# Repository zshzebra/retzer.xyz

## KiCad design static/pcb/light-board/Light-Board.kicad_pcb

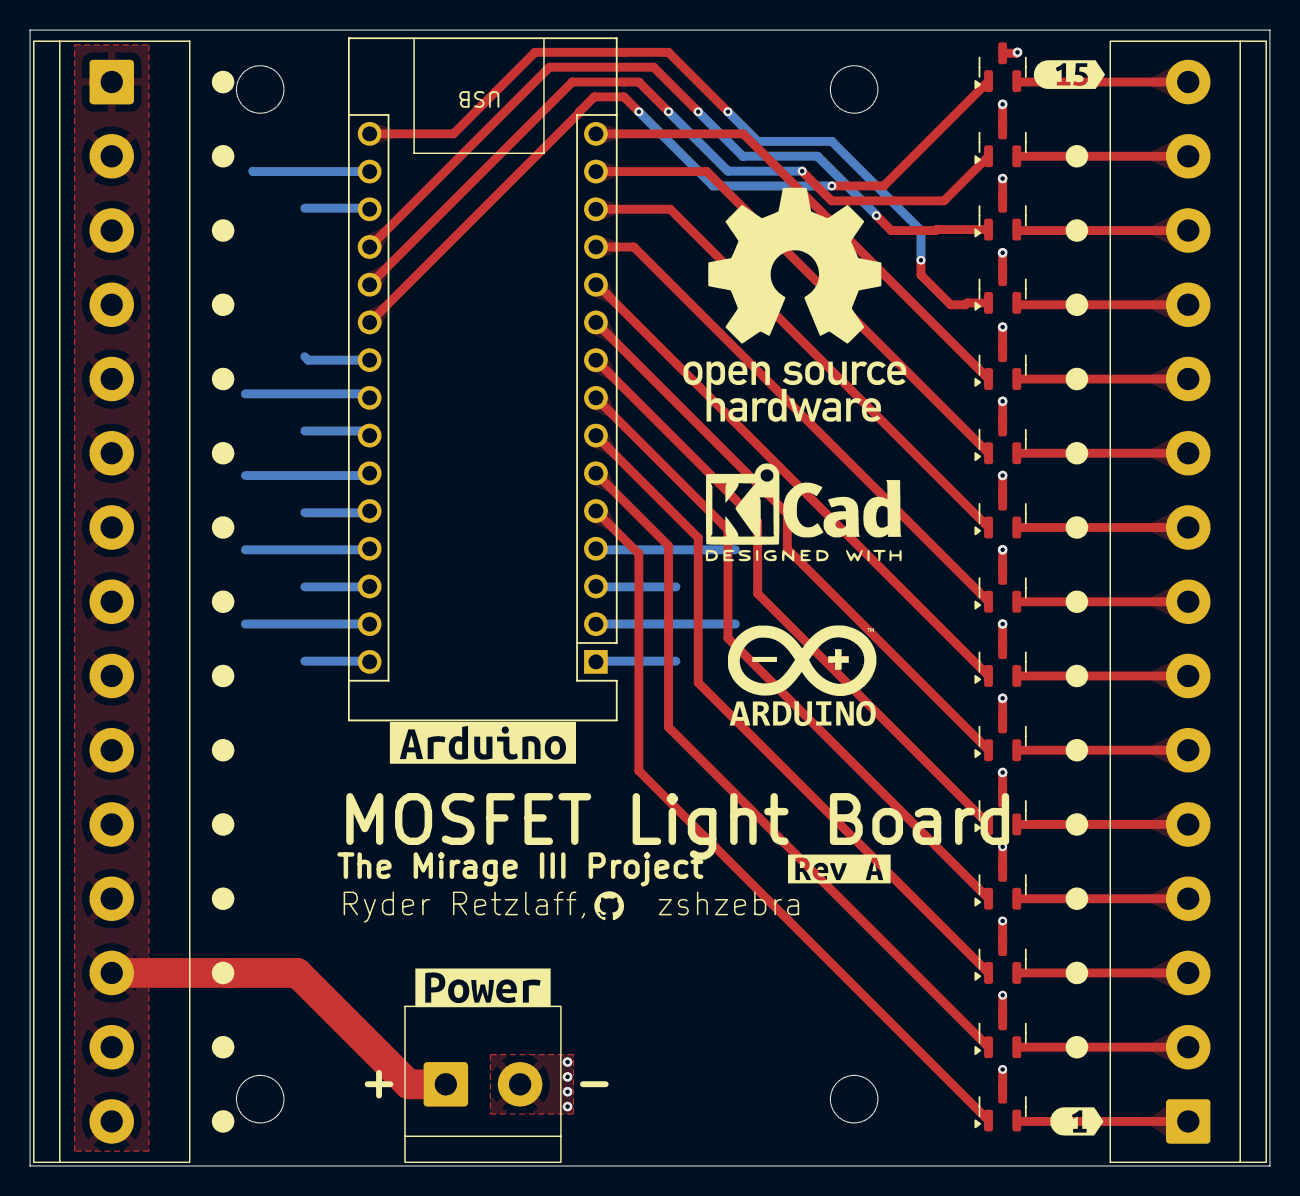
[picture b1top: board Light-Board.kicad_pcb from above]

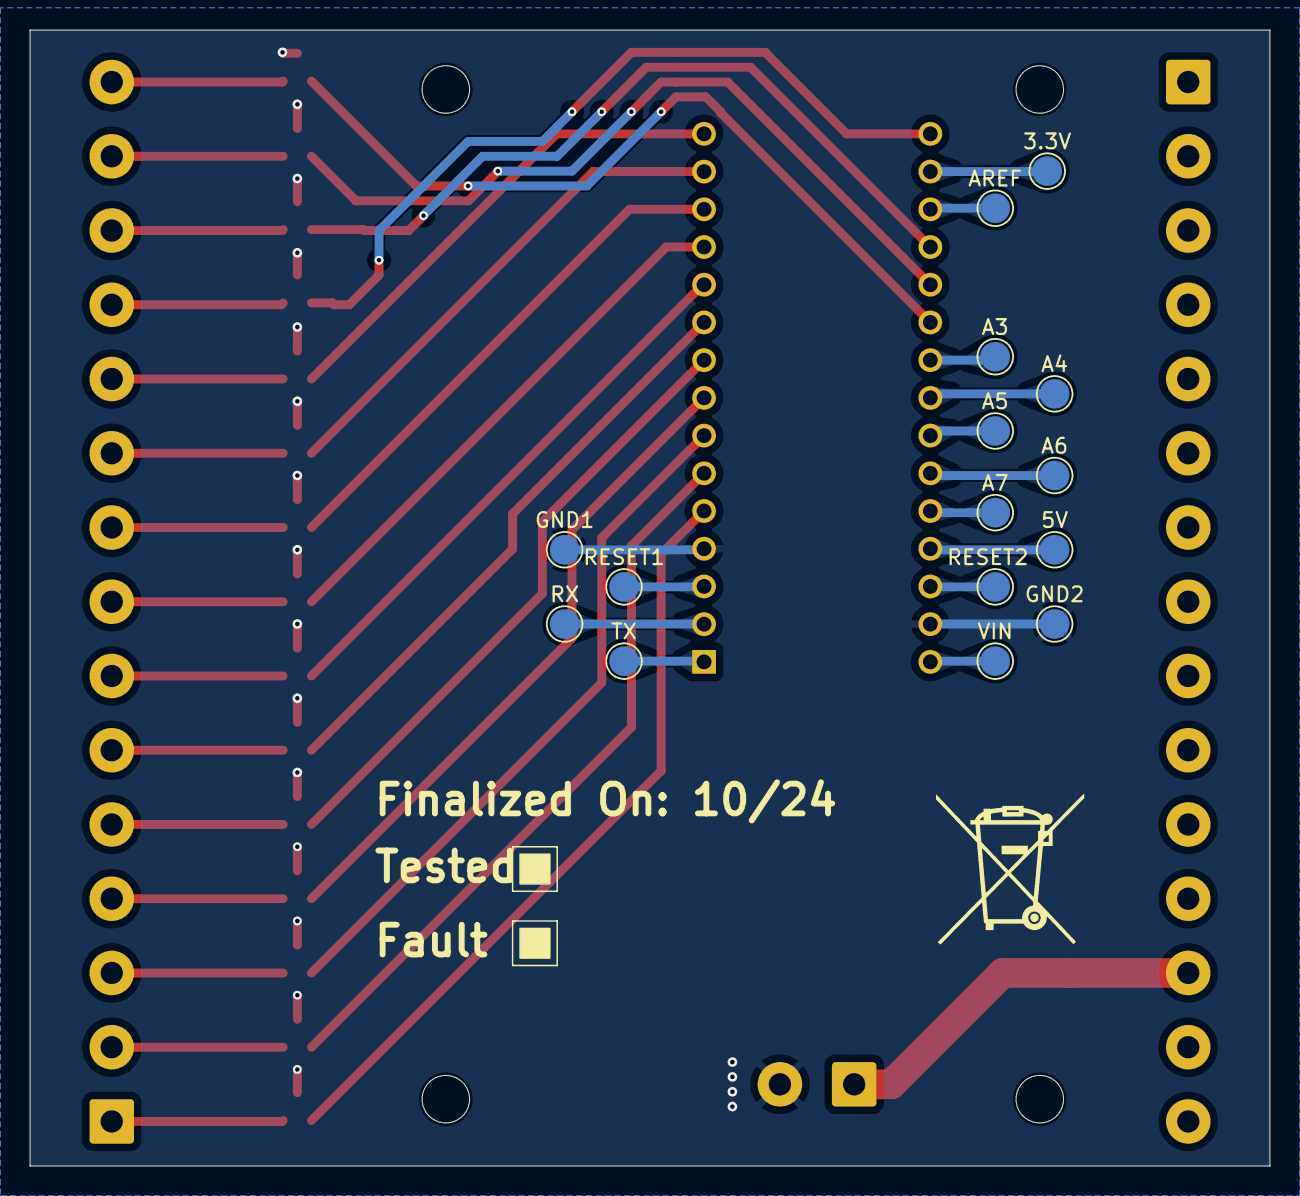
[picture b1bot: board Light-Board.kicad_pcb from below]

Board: 2 copper layers, 83.5 x 76.5 mm, 43 parts (15 on the bottom side), 45 nets.

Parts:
3.3V, 5V: TestPoint; TestPoint_Pad_D2.0mm
 RESET1: TestPoint; TestPoint_Pad_D2.0mm
A1: Arduino_Nano_v2.x; Arduino_Nano
A3, A4, A5, A6, A7: TestPoint; TestPoint_Pad_D2.0mm
AREF: TestPoint; TestPoint_Pad_D2.0mm
GND1, GND2: TestPoint; TestPoint_Pad_D2.0mm
H1, H2, H3, H4: MountingHole; MountingHole_3.2mm_M3
J1, J4: Screw_Terminal_01x15; TerminalBlock_01x15
J2: Screw_Terminal_01x02; TerminalBlock_01x2
Q1, Q2, Q3, Q4, Q5, Q6, Q7, Q8, Q9, Q10, Q11, Q12, Q13, Q14, Q15: SK359AN; SOT-23
RESET2: TestPoint; TestPoint_Pad_D2.0mm
RX: TestPoint; TestPoint_Pad_D2.0mm
TX: TestPoint; TestPoint_Pad_D2.0mm
VIN: TestPoint; TestPoint_Pad_D2.0mm
kibuzzard-67197C5A: G***; kibuzzard-67197C5A
kibuzzard-671860AF: G***; kibuzzard-671860AF
kibuzzard-671861A2: G***; kibuzzard-671861A2
kibuzzard-67186087: G***; kibuzzard-67186087
kibuzzard-67186155: G***; kibuzzard-67186155

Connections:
/M1_Drain: J1.1, Q1.2 (Source)
/M1_Gate: A1.5 (D2), Q1.1 (Gate)
/M2_Drain: J1.2, Q2.2 (Source)
/M2_Gate: A1.6 (D3), Q2.1 (Gate)
/M3_Drain: J1.3, Q3.2 (Source)
/M3_Gate: A1.7 (D4), Q3.1 (Gate)
/M4_Drain: J1.4, Q4.2 (Source)
/M4_Gate: A1.8 (D5), Q4.1 (Gate)
/M5_Drain: J1.5, Q5.2 (Source)
/M5_Gate: A1.9 (D6), Q5.1 (Gate)
/M6_Drain: J1.6, Q6.2 (Source)
/M6_Gate: A1.10 (D7), Q6.1 (Gate)
/M7_Drain: J1.7, Q7.2 (Source)
/M7_Gate: A1.11 (D8), Q7.1 (Gate)
/M8_Drain: J1.8, Q8.2 (Source)
/M8_Gate: A1.12 (D9), Q8.1 (Gate)
/M9_Drain: J1.9, Q9.2 (Source)
/M9_Gate: A1.13 (D10), Q9.1 (Gate)
/M10_Drain: J1.10, Q10.2 (Source)
/M10_Gate: A1.14 (D11), Q10.1 (Gate)
/M11_Drain: J1.11, Q11.2 (Source)
/M11_Gate: A1.15 (D12), Q11.1 (Gate)
/M12_Drain: J1.12, Q12.2 (Source)
/M12_Gate: A1.16 (D13), Q12.1 (Gate)
/M13_Drain: J1.13, Q13.2 (Source)
/M13_Gate: A1.19 (A0), Q13.1 (Gate)
/M14_Drain: J1.14, Q14.2 (Source)
/M14_Gate: A1.20 (A1), Q14.1 (Gate)
/M15_Drain: J1.15, Q15.2 (Source)
/M15_Gate: A1.21 (A2), Q15.1 (Gate)
GND: A1.4 (GND), A1.29 (GND), GND1.1, GND2.1, J2.2, Q1.3 (Drain), Q2.3 (Drain), Q3.3 (Drain), Q4.3 (Drain), Q5.3 (Drain), Q6.3 (Drain), Q7.3 (Drain), Q8.3 (Drain), Q9.3 (Drain), Q10.3 (Drain), Q11.3 (Drain), Q12.3 (Drain), Q13.3 (Drain), Q14.3 (Drain), Q15.3 (Drain)
unnamed: 3.3V.1, A1.17 (3V3)
unnamed: 5V.1, A1.27 (+5V)
unnamed: A1.22 (A3), A3.1
unnamed: A1.23 (A4), A4.1
unnamed: A1.24 (A5), A5.1
unnamed: A1.25 (A6), A6.1
unnamed: A1.26 (A7), A7.1
unnamed: A1.18 (AREF), AREF.1
unnamed: A1.2 (D0/RX), RX.1
unnamed: A1.1 (D1/TX), TX.1
unnamed: A1.30 (VIN), VIN.1
unnamed: RESET1.1, A1.3 (~RESET)
unnamed: A1.28 (~RESET), RESET2.1
VCC: J2.1, J4.1, J4.2, J4.3, J4.4, J4.5, J4.6, J4.7, J4.8, J4.9, J4.10, J4.11, J4.12, J4.13, J4.14, J4.15

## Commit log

2024-09-21 Setup Project
2024-09-21 Allow for manual site build
2024-09-21 Fix branch name
2024-09-21 Add CNAME
2024-09-21 Fix Typo
2024-09-21 Add permissions to action
2024-09-21 Update deploy workflow
2024-09-21 Update theme
2024-09-21 Update submodule
2024-09-21 Change workflow
2024-09-21 Update permissions
2024-09-21 Fix action
2024-09-21 Update upload pages artifact
2024-09-21 Release
2024-11-12 Update CNAME
2024-11-13 Weeee
2024-12-07 Add minecraft server
